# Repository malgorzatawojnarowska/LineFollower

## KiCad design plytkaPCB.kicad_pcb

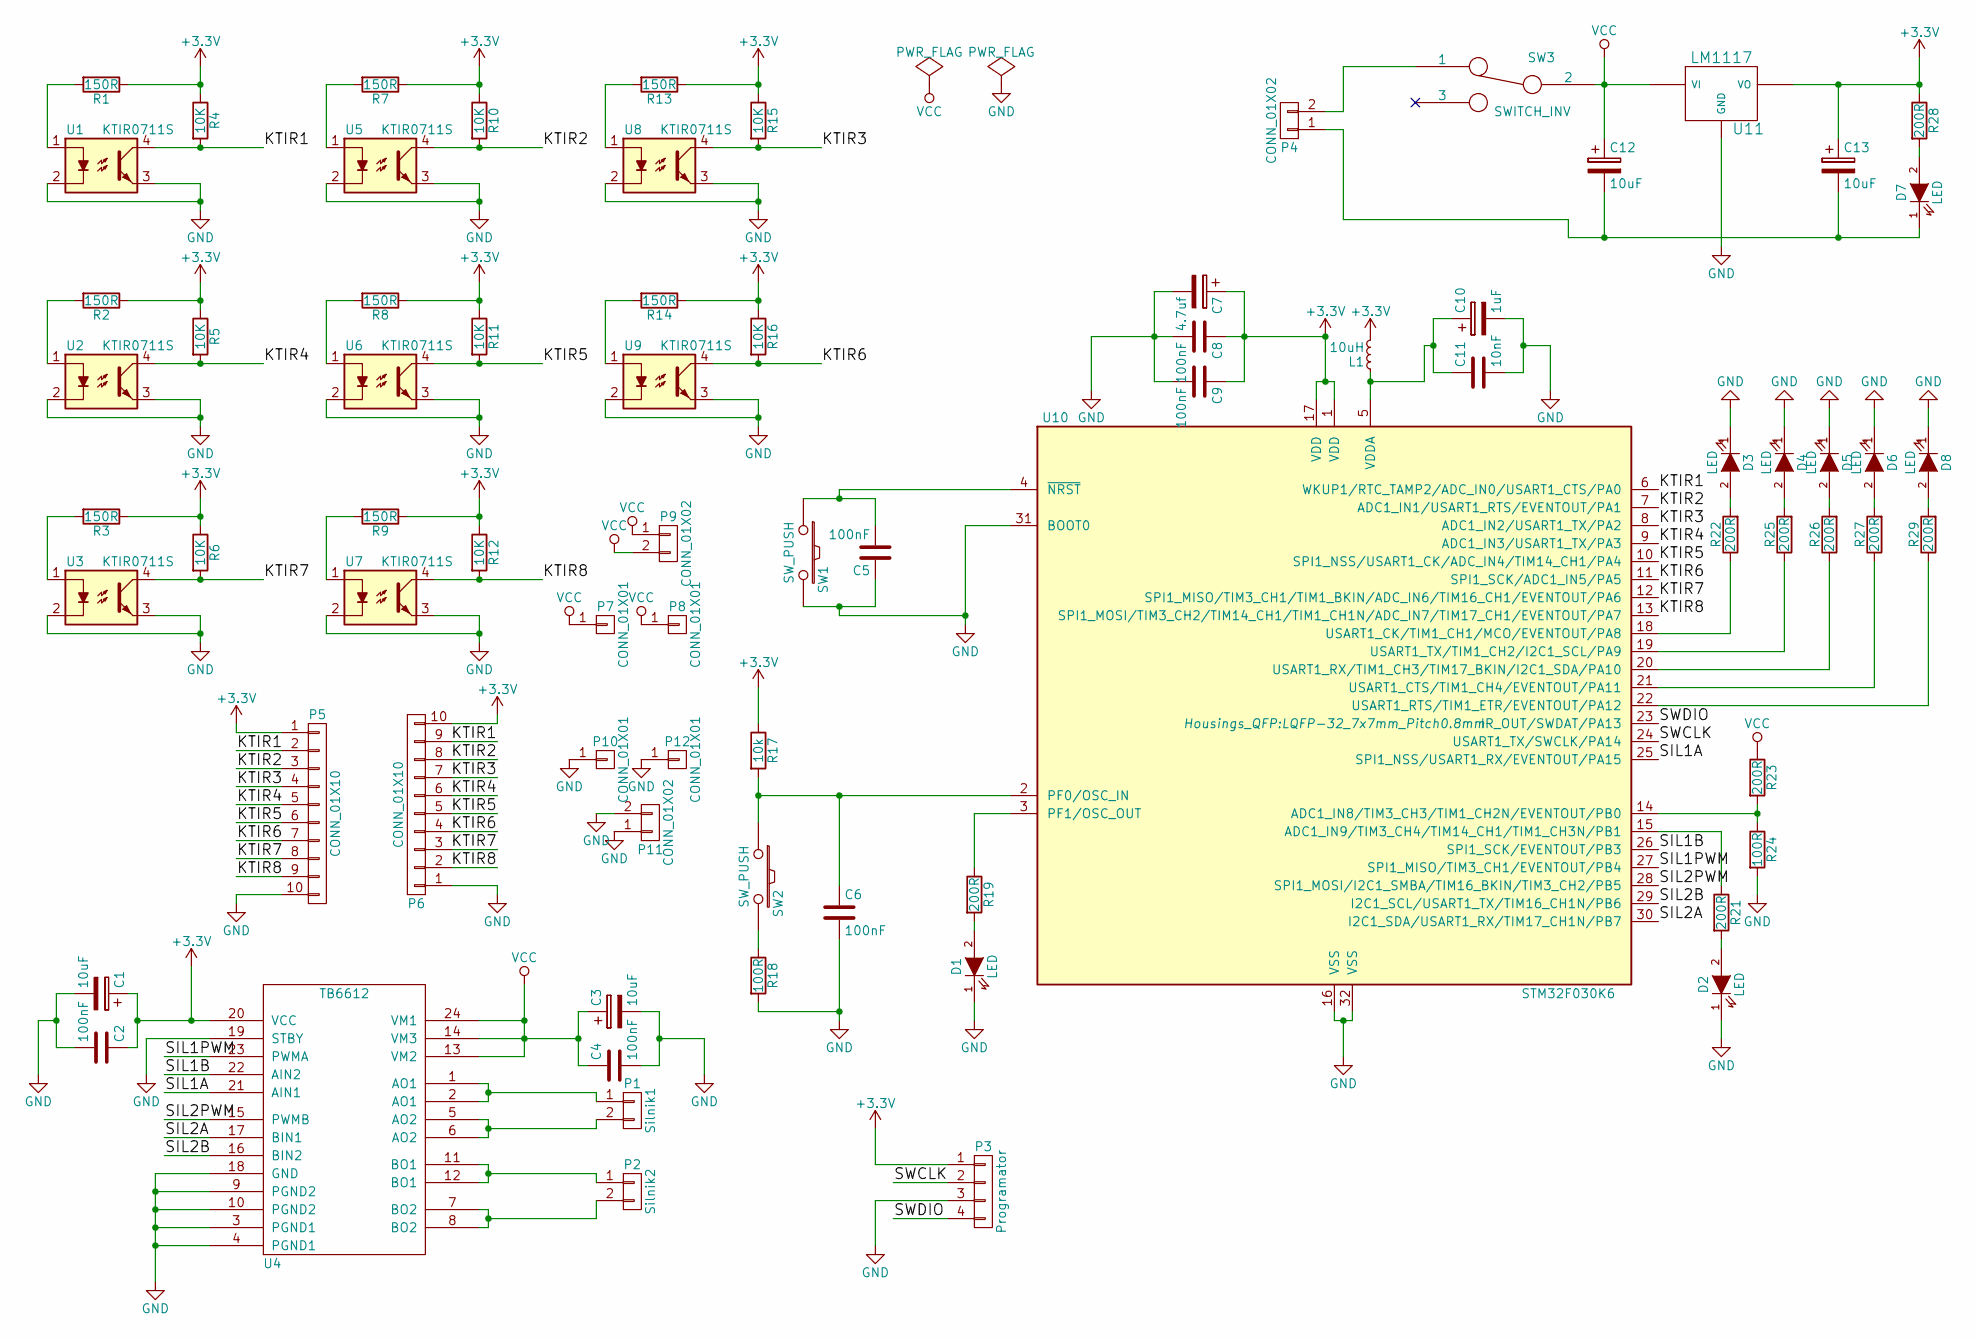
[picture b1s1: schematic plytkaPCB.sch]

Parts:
C1, C3, C12, C13: 10uF; TantalC_SizeA_EIA-3216_HandSoldering
C2, C4, C5, C6, C8, C9: 100nF; C_0805
C7: 4.7uf; TantalC_SizeA_EIA-3216_HandSoldering
C10: 1uF; TantalC_SizeA_EIA-3216_HandSoldering
C11: 10nF; C_0805
D1, D2, D3, D4, D5, D6, D7, D8: LED; LED-0805
L1: 10uH; R_1206_HandSoldering
P1: Silnik1; Pin_Header_Straight_1x02
P2: Silnik2; Pin_Header_Straight_1x02
P3: Programator; Pin_Header_Straight_1x04
P4: CONN_01X02; zl_zasilania
P5, P6: CONN_01X10; fpc_10_pin
P7, P8, P10, P12: CONN_01X01; conn1x1
P9, P11: CONN_01X02; conn1x2
R1, R2, R3, R7, R8, R9, R13, R14: 150R; R_0805_HandSoldering
R4, R5, R6, R10, R11, R12, R15, R16: 10K; R_0805_HandSoldering
R17: 10k; R_0805_HandSoldering
R18, R24: 100R; R_0805_HandSoldering
R19, R21, R22, R23, R25, R26, R27, R28, R29: 200R; R_0603_HandSoldering
SW1, SW2: SW_PUSH; tact_switch_smd
SW3: SWITCH_INV; przelacznik_smd
U1, U2, U3, U5, U6, U7, U8, U9: KTIR0711S
U4: TB6612
U10: STM32F030K6; LQFP-32_7x7mm_Pitch0.8mm
U11: LM1117; LM1117_SOT223

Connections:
+3V3: C1.1, C2.1, C7.1, C8.1, C9.1, C13.1, L1.2, P3.1, P5.1, P6.10, R1.1, R2.1, R3.1, R4.1, R5.1, R6.1, R7.1, R8.1, R9.1, R10.1, R11.1, R12.1, R13.1, R14.1, R15.1, R16.1, R17.1, R28.1, U4.20 (VCC), U10.1 (VDD), U10.17 (VDD), U11.2 (VO)
/KTIR1: P5.2, P6.9, R4.2, U1.4, U10.6 (WKUP1/RTC_TAMP2/ADC_IN0/USART1_CTS/PA0)
/KTIR2: P5.3, P6.8, R10.2, U5.4, U10.7 (ADC1_IN1/USART1_RTS/EVENTOUT/PA1)
/KTIR3: P5.4, P6.7, R15.2, U8.4, U10.8 (ADC1_IN2/USART1_TX/PA2)
/KTIR4: P5.5, P6.6, R5.2, U2.4, U10.9 (ADC1_IN3/USART1_TX/PA3)
/KTIR5: P5.6, P6.5, R11.2, U6.4, U10.10 (SPI1_NSS/USART1_CK/ADC_IN4/TIM14_CH1/PA4)
/KTIR6: P5.7, P6.4, R16.2, U9.4, U10.11 (SPI1_SCK/ADC1_IN5/PA5)
/KTIR7: P5.8, P6.3, R6.2, U3.4, U10.12 (SPI1_MISO/TIM3_CH1/TIM1_BKIN/ADC_IN6/TI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)
/KTIR8: P5.9, P6.2, R12.2, U7.4, U10.13 (SPI1_MOSI/TIM3_CH2/TIM14_CH1/TIM1_CH1N/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)
/SIL1A: U4.21 (AIN1), U10.25 (SPI1_NSS/USART1_RX/EVENTOUT/PA15)
/SIL1B: U4.22 (AIN2), U10.26 (SPI1_SCK/EVENTOUT/PB3)
/SIL1PWM: U4.23 (PWMA), U10.27 (SPI1_MISO/TIM3_CH1/EVENTOUT/PB4)
/SIL2A: U4.17 (BIN1), U10.30 (I2C1_SDA/USART1_RX/TIM17_CH1N/PB7)
/SIL2B: U4.16 (BIN2), U10.29 (I2C1_SCL/USART1_TX/TIM16_CH1N/PB6)
/SIL2PWM: U4.15 (PWMB), U10.28 (SPI1_MOSI/I2C1_SMBA/TIM16_BKIN/TIM3_CH2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)
/SWCLK: P3.2, U10.24 (USART1_TX/SWCLK/PA14)
/SWDIO: P3.4, U10.23 (IR_OUT/SWDAT/PA13)
GND: C1.2, C2.2, C3.2, C4.2, C5.1, C6.2, C7.2, C8.2, C9.2, C10.2, C11.2, D1.1 (K), D2.1 (K), D3.1 (K), D4.1 (K), D5.1 (K), D6.1 (K), D8.1 (K), P3.3, P5.10, P6.1, P10.1, P11.1, P11.2, P12.1, R18.2, R24.2, SW1.2, U1.2, U1.3, U2.2, U2.3, U3.2, U3.3, U4.3 (PGND1), U4.4 (PGND1), U4.9 (PGND2), U4.10 (PGND2), U4.18 (GND), U4.19 (STBY), U5.2, U5.3, U6.2, U6.3, U7.2, U7.3, U8.2, U8.3, U9.2, U9.3, U10.16 (VSS), U10.31 (BOOT0), U10.32 (VSS), U11.3 (GND)
unnamed: C5.2, SW1.1, U10.4 (~NRST)
unnamed: C6.1, R17.2, SW2.1, U10.2 (PF0/OSC_IN)
unnamed: C10.1, C11.1, L1.1, U10.5 (VDDA)
unnamed: C12.2, C13.2, D7.1 (K), P4.1
unnamed: D1.2 (A), R19.2
unnamed: D2.2 (A), R21.2
unnamed: D3.2 (A), R22.2
unnamed: D4.2 (A), R25.2
unnamed: D5.2 (A), R26.2
unnamed: D6.2 (A), R27.2
unnamed: D7.2 (A), R28.2
unnamed: D8.2 (A), R29.2
unnamed: P1.1, U4.1 (AO1), U4.2 (AO1)
unnamed: P1.2, U4.5 (AO2), U4.6 (AO2)
unnamed: P2.1, U4.11 (BO1), U4.12 (BO1)
unnamed: P2.2, U4.7 (BO2), U4.8 (BO2)
unnamed: P4.2, SW3.1
unnamed: R1.2, U1.1
unnamed: R2.2, U2.1
unnamed: R3.2, U3.1
unnamed: R7.2, U5.1
unnamed: R8.2, U6.1
unnamed: R9.2, U7.1
unnamed: R13.2, U8.1
unnamed: R14.2, U9.1
unnamed: R18.1, SW2.2
unnamed: R19.1, U10.3 (PF1/OSC_OUT)
unnamed: R21.1, U10.15 (ADC1_IN9/TIM3_CH4/TIM14_CH1/TIM1_CH3N/P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)
unnamed: R22.1, U10.18 (USART1_CK/TIM1_CH1/MCO/EVENTOUT/PA8)
unnamed: R23.2, R24.1, U10.14 (ADC1_IN8/TIM3_CH3/TIM1_CH2N/EVENTOUT/PB0)
unnamed: R25.1, U10.19 (USART1_TX/TIM1_CH2/I2C1_SCL/PA9)
unnamed: R26.1, U10.20 (USART1_RX/TIM1_CH3/TIM17_BKIN/I2C1_SDA/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)
unnamed: R27.1, U10.21 (USART1_CTS/TIM1_CH4/EVENTOUT/PA11)
unnamed: R29.1, U10.22 (USART1_RTS/TIM1_ETR/EVENTOUT/PA12)
VCC: C3.1, C4.1, C12.1, P7.1, P8.1, P9.1, P9.2, R23.1, SW3.2, U4.13 (VM2), U4.14 (VM3), U4.24 (VM1), U11.1 (VI)

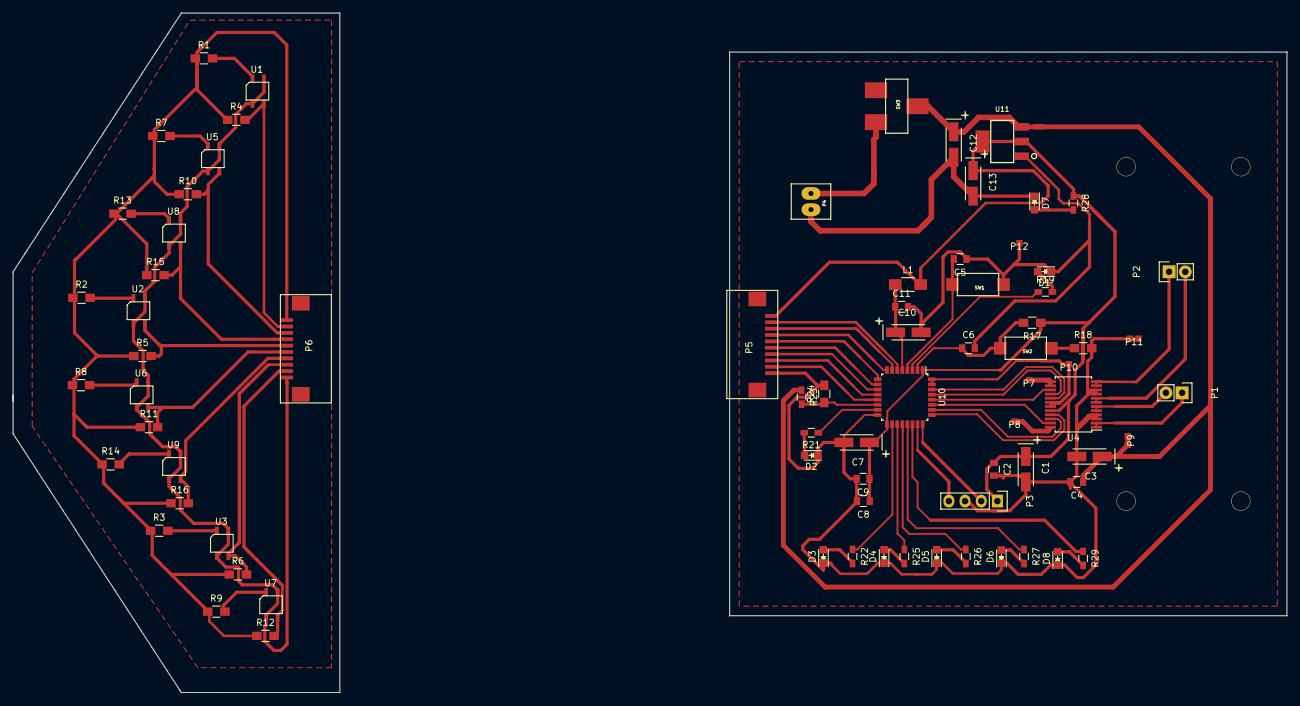
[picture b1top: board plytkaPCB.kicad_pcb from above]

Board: 2 copper layers, 200.0 x 106.7 mm, 76 parts (0 on the bottom side), 53 nets.

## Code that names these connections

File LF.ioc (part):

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Mcu.Name=STM32F030K6Tx
Mcu.Package=LQFP32
Mcu.UserName=STM32F030K6Tx
PA0.GPIOParameters=GPIO_Label
PA0.GPIO_Label=KTIR1
PA0.Mode=IN0
PA0.Signal=ADC_IN0
PA1.GPIOParameters=GPIO_Label
PA1.GPIO_Label=KTIR2
PA1.Mode=IN1
PA1.Signal=ADC_IN1
PA10.GPIOParameters=GPIO_Label
PA10.GPIO_Label=LED5
PA10.Signal=GPIO_Output
PA11.GPIOParameters=GPIO_Label
PA11.GPIO_Label=LED6
PA11.Signal=GPIO_Output
PA12.GPIOParameters=GPIO_Label
PA12.GPIO_Label=LED7
PA12.Signal=GPIO_Output
PA13.GPIOParameters=GPIO_Label
PA13.GPIO_Label=SWDIO
PA13.Mode=Serial_Wire
PA13.Signal=SYS_SWDIO
PA14.GPIOParameters=GPIO_Label
PA14.GPIO_Label=SWCLK
PA14.Mode=Serial_Wire
PA14.Signal=SYS_SWCLK
PA15.GPIOParameters=GPIO_Label
PA15.GPIO_Label=SIL1A
PA15.Signal=GPIO_Output
PA2.GPIOParameters=GPIO_Label
PA2.GPIO_Label=KTIR3
PA2.Mode=IN2
PA2.Signal=ADC_IN2
PA3.GPIOParameters=GPIO_Label
PA3.GPIO_Label=KTIR4
PA3.Mode=IN3
PA3.Signal=ADC_IN3
PA4.GPIOParameters=GPIO_Label
PA4.GPIO_Label=KTIR5
PA4.Mode=IN4
PA4.Signal=ADC_IN4
PA5.GPIOParameters=GPIO_Label
PA5.GPIO_Label=KTIR6
PA5.Mode=IN5
PA5.Signal=ADC_IN5
PA6.GPIOParameters=GPIO_Label
PA6.GPIO_Label=KTIR7
PA6.Mode=IN6
PA6.Signal=ADC_IN6
PA7.GPIOParameters=GPIO_Label
PA7.GPIO_Label=KTIR8
PA7.Mode=IN7
PA7.Signal=ADC_IN7
PA8.GPIOParameters=GPIO_Label
PA8.GPIO_Label=LED3
PA8.Signal=GPIO_Output
PA9.GPIOParameters=GPIO_Label
PA9.GPIO_Label=LED4
PA9.Signal=GPIO_Output
PB0.GPIOParameters=GPIO_Label
PB0.GPIO_Label=BATTERY
PB0.Mode=IN8
PB0.Signal=ADC_IN8
PB1.GPIOParameters=GPIO_Label
PB1.GPIO_Label=LED2
PB1.Signal=GPIO_Output
PB3.GPIOParameters=GPIO_Label
PB3.GPIO_Label=SIL1B
PB3.Signal=GPIO_Output
PB4.GPIOParameters=GPIO_Label
PB4.GPIO_Label=PWM2
PB4.Signal=S_TIM3_CH1
PB5.GPIOParameters=GPIO_Label
PB5.GPIO_Label=PWM1
PB5.Signal=S_TIM3_CH2
PB6.GPIOParameters=GPIO_Label
PB6.GPIO_Label=SIL2B
PB6.Signal=GPIO_Output
PB7.GPIOParameters=GPIO_Label
PB7.GPIO_Label=SIL2A
PB7.Signal=GPIO_Output
PF0-OSC_IN.GPIOParameters=GPIO_Label
PF0-OSC_IN.GPIO_Label=BUTTON
PF0-OSC_IN.Signal=GPXTI0
PF1-OSC_OUT.GPIOParameters=GPIO_Label
PF1-OSC_OUT.GPIO_Label=LED1
PF1-OSC_OUT.Signal=GPIO_Output

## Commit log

2019-11-28 Create project
